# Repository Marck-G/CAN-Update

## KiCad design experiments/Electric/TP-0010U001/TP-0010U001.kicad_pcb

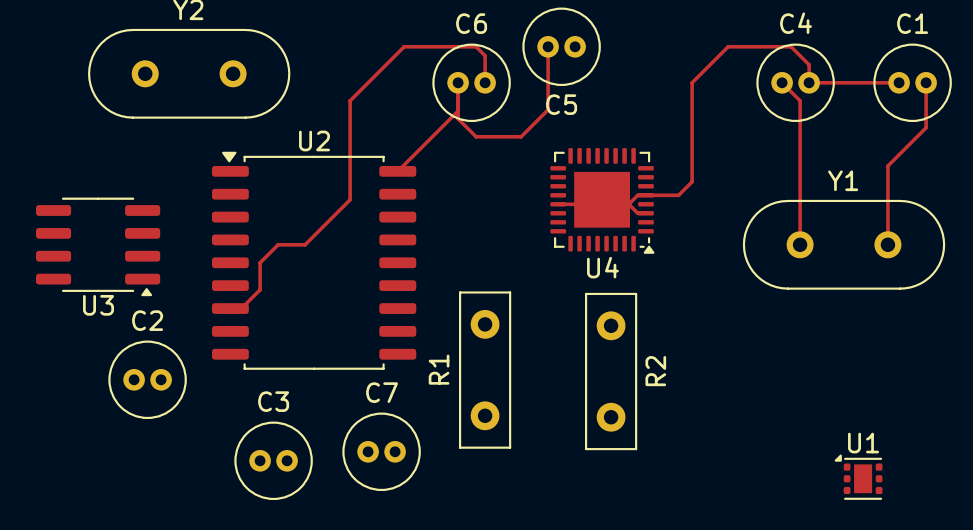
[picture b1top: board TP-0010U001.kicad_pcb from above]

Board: 2 copper layers, 15 parts (0 on the bottom side), 11 nets.

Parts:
C1, C4, C6, C7: 22pF; C_Radial_D4.0mm_H5.0mm_P1.50mm
C2, C3, C5: 0,1 uF; C_Radial_D4.0mm_H5.0mm_P1.50mm
R1: 4,7K; R_Box_L8.4mm_W2.5mm_P5.08mm
R2: 4,7 K; R_Box_L8.4mm_W2.5mm_P5.08mm
U1: TMP117xxDRV; WSON-6-1EP_2x2mm_P0.65mm_EP1x1.6mm
U2: MCP2515-xSO; SOIC-18W_7.5x11.6mm_P1.27mm
U3: TJA1051T; SOIC-8_3.9x4.9mm_P1.27mm
U4: ATmega328P-M; QFN-32-1EP_5x5mm_P0.5mm_EP3.1x3.1mm
Y1: 16MHz; Crystal_HC49-U_Vertical
Y2: 8 MHz; Crystal_HC49-U_Vertical

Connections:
GND: C1.1, C2.1, C3.2, C4.2, C5.2, C6.1, C7.2, U1.2 (GND), U2.18 (VDD), U3.2 (GND), U4.3 (GND), U4.5 (GND), U4.21 (GND), U4.33 (GND)
unnamed: U1.3 (ALERT), U4.32 (PD2)
unnamed: R2.1, U1.1 (SCL), U4.28 (PC5)
unnamed: R1.2, U1.6 (SDA), U4.27 (PC4)
unnamed: C7.1, U2.8 (OSC1), Y2.1
unnamed: C6.2, U2.7 (OSC2), Y2.2
unnamed: U2.2 (RXCAN), U3.4 (RXD)
unnamed: U2.1 (TXCAN), U3.1 (TXD)
unnamed: C1.2, U4.7 (XTAL1/PB6), Y1.2
unnamed: C4.1, U4.8 (XTAL2/PB7), Y1.1
VCC: C2.2, C3.1, C5.1, R1.1, R2.2, U1.5 (V+), U2.9 (VSS), U4.4 (VCC), U4.6 (VCC), U4.18 (AVCC), U4.20 (AREF)

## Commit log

2025-09-17 backup 2025-09-16
